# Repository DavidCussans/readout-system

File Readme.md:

SoLid readout system
====================

_Development of the readout system for the full scale SoLid experiment._

The repository is split into the separate development parts:

* sensors - The light sensors and the PCBs
* analog board - to provide bias voltage, amplify and shape the analog signals form the sensors
* digital board - to digitise the analog signals, analyse the signals in an FPGA to make trigger decisions and transmit them to a PC
* software - to collect data transmitted from the FPGA, further reduce the data and write it to disk. The interface for operators to control the system
* cabling - to connect the senors to the analog board, the analog board to the digital board, power supplies to each board, etc.
* docs - system level documents such as requirements, reports, etc.
* utility_box   design info and documentation about the utility box

Permissions
-----------

The `Readout developers` group have write access, other members of the collaboration have read access.
If you need access contact Dan Saunders.

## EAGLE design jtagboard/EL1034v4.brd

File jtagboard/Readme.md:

Documentation about JTAG board.

Design files in Eagle.

Cable needed to control multiplexer. See https://docs.google.com/spreadsheets/d/1sPC1HHSBhcLIxRam0Nl7j7j9OBzJNn8TZ3wjZsIO86E/edit?usp=sharing

Script to set up Minnowboard GPIO: setup_gpio.sh

Script to select which HDMI interface is used: test_jtag_mltxer.py

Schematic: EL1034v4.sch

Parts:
C1, C4, C36: 100u; EIA7343
C2, C3, C5, C6, C7, C8, C9, C10, C11, C12, C13, C14, C15, C16, C17, C18, C19, C20, C21, C22, C23, C24, C25, C26, C27, C28, C29, C30, C31, C32, C33, C34, C35, C37: 100n; 0805
CON1: SL5.08/2
D1, D2, D3, D4, D5, D6, D7, D8, D9: RED; LED-0603
HDMI0, HDMI1, HDMI2, HDMI3, HDMI4, HDMI5, HDMI6, HDMI7, HDMI8, HDMI9: 47266-0001
IC1, IC3, IC5, IC7, IC9, IC11, IC13, IC15, IC17, IC19: DS90LV031ATMX; SOIC127P600X175-16N
IC2, IC4, IC6, IC8, IC10, IC12, IC14, IC16, IC18, IC20: SN65LVDT2DBVT; SOT95P280X145-5N
IC21, IC22, IC23, IC24, IC25, IC26, IC27, IC28: 74LV4051PW; TSSOP16
IC29: LM3940; TO220-IGO
IC30: 74LVC1G14SE-7; SOT65P210X110-5N
JP1, JP2, JP3, JP4, JP5, JP6, JP7, JP8, JP9, JP10, JP11: M06POLAR; MOLEX-1X6
JP12, JP13: M02POLAR; MOLEX-1X2
MOD1: JTAG-SMT2; JTAG_SMT2
R1, R3, R5, R7, R9, R30, R32, R34, R36, R38, R40, R42, R44, R46, R48, R50, R52, R54, R56, R58, R60, R62, R64, R66, R68, R70, R72, R74, R76, R78: DNF; 0603-RES
R2, R4, R6, R8, R10, R31, R33, R35, R37, R39, R41, R43, R45, R47, R49, R51, R53, R55, R57, R59, R61, R63, R65, R67, R69, R71, R73, R75, R77, R79: 100k; 0603-RES
R11, R12, R13, R14, R15, R16, R17, R18, R19, R20: 10k; 0603-RES
R21, R22, R23, R24, R25, R26, R27, R28, R29: 2K2; 0603-RES
SJ1, SJ2, SJ3, SJ4, SJ5, SJ6, SJ7, SJ8, SJ9, SJ10, SJ11, SJ12, SJ13: SOLDERJUMPERNO; SJ_2S-NO
STANDOFF1, STANDOFF2, STANDOFF3, STANDOFF4, STANDOFF5, STANDOFF6, STANDOFF7: STAND-OFF
TP1, TP2: TEST-POINTTP_15TH_THRU; TP_15TH

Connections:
3.3V: C3.1, C4.A (+), C5.1, C6.1, C7.1, C8.1, C9.1, C10.1, C11.1, C12.1, C13.1, C14.2, C15.2, C16.2, C17.2, C18.2, C19.2, C20.2, C21.2, C22.2, C23.2, C24.2, C25.2, C26.2, C27.2, C28.2, C29.2, C30.2, C31.2, C32.2, C33.2, C34.2, C35.1, C36.A (+), C37.1, D9.A, IC1.4 (EN), IC1.16 (VCC), IC2.1 (VCC), IC3.4 (EN), IC3.16 (VCC), IC4.1 (VCC), IC5.4 (EN), IC5.16 (VCC), IC6.1 (VCC), IC7.4 (EN), IC7.16 (VCC), IC8.1 (VCC), IC9.4 (EN), IC9.16 (VCC), IC10.1 (VCC), IC11.4 (EN), IC11.16 (VCC), IC12.1 (VCC), IC13.4 (EN), IC13.16 (VCC), IC14.1 (VCC), IC15.4 (EN), IC15.16 (VCC), IC16.1 (VCC), IC17.4 (EN), IC17.16 (VCC), IC18.1 (VCC), IC19.4 (EN), IC19.16 (VCC), IC20.1 (VCC), IC21.16 (VCC), IC22.16 (VCC), IC23.16 (VCC), IC24.16 (VCC), IC25.16 (VCC), IC26.16 (VCC), IC27.16 (VCC), IC28.16 (VCC), IC29.OUT, IC30.5 (VCC), JP12.2, JP13.2, MOD1.9 (VREF), MOD1.11 (VDD), R1.2, R3.2, R5.2, R7.2, R9.2, R11.2, R12.2, R13.2, R14.2, R15.2, R16.2, R17.2, R18.2, R19.2, R20.2, R30.2, R32.2, R34.2, R36.2, R38.2, R40.2, R42.2, R44.2, R46.2, R48.2, R50.2, R52.2, R54.2, R56.2, R58.2, R60.2, R62.2, R64.2, R66.2, R68.2, R70.2, R72.2, R74.2, R76.2, R78.2, TP1.P$1
5V_IN: C1.A (+), C2.1, CON1.P$1, IC29.IN, JP1.2
!S3: IC22.6 (!E), IC24.6 (!E), IC26.6 (!E), IC28.6 (!E), IC30.4 (Y)
GND: C1.C (-), C2.2, C3.2, C4.C (-), C5.2, C6.2, C7.2, C8.2, C9.2, C10.2, C11.2, C12.2, C13.2, C14.1, C15.1, C16.1, C17.1, C18.1, C19.1, C20.1, C21.1, C22.1, C23.1, C24.1, C25.1, C26.1, C27.1, C28.1, C29.1, C30.1, C31.1, C32.1, C33.1, C34.1, C35.2, C36.C (-), C37.2, CON1.P$2, HDMI0.2, HDMI0.5, HDMI0.8, HDMI0.11, HDMI0.13, HDMI0.14, HDMI0.17, HDMI0.18, HDMI0.19, HDMI0.SHELL1, HDMI0.SHELL2, HDMI0.SHELL3, HDMI0.SHELL4, HDMI1.2, HDMI1.5, HDMI1.8, HDMI1.11, HDMI1.13, HDMI1.14, HDMI1.17, HDMI1.18, HDMI1.19, HDMI1.SHELL1, HDMI1.SHELL2, HDMI1.SHELL3, HDMI1.SHELL4, HDMI2.2, HDMI2.5, HDMI2.8, HDMI2.11, HDMI2.13, HDMI2.14, HDMI2.17, HDMI2.18, HDMI2.19, HDMI2.SHELL1, HDMI2.SHELL2, HDMI2.SHELL3, HDMI2.SHELL4, HDMI3.2, HDMI3.5, HDMI3.8, HDMI3.11, HDMI3.13, HDMI3.14, HDMI3.17, HDMI3.18, HDMI3.19, HDMI3.SHELL1, HDMI3.SHELL2, HDMI3.SHELL3, HDMI3.SHELL4, HDMI4.2, HDMI4.5, HDMI4.8, HDMI4.11, HDMI4.13, HDMI4.14, HDMI4.17, HDMI4.18, HDMI4.19, HDMI4.SHELL1, HDMI4.SHELL2, HDMI4.SHELL3, HDMI4.SHELL4, HDMI5.2, HDMI5.5, HDMI5.8, HDMI5.11, HDMI5.13, HDMI5.14, HDMI5.17, HDMI5.18, HDMI5.19, HDMI5.SHELL1, HDMI5.SHELL2, HDMI5.SHELL3, HDMI5.SHELL4, HDMI6.2, HDMI6.5, HDMI6.8, HDMI6.11, HDMI6.13, HDMI6.14, HDMI6.17, HDMI6.18, HDMI6.19, HDMI6.SHELL1, HDMI6.SHELL2, HDMI6.SHELL3, HDMI6.SHELL4, HDMI7.2, HDMI7.5, HDMI7.8, HDMI7.11, HDMI7.13, HDMI7.14, HDMI7.17, HDMI7.18, HDMI7.19, HDMI7.SHELL1, HDMI7.SHELL2, HDMI7.SHELL3, HDMI7.SHELL4, HDMI8.2, HDMI8.5, HDMI8.8, HDMI8.11, HDMI8.13, HDMI8.14, HDMI8.17, HDMI8.18, HDMI8.19, HDMI8.SHELL1, HDMI8.SHELL2, HDMI8.SHELL3, HDMI8.SHELL4, HDMI9.2, HDMI9.5, HDMI9.8, HDMI9.11, HDMI9.13, HDMI9.14, HDMI9.17, HDMI9.18, HDMI9.19, HDMI9.SHELL1, HDMI9.SHELL2, HDMI9.SHELL3, HDMI9.SHELL4, IC1.8 (GND), IC1.12 (~EN), IC2.2 (GND), IC3.8 (GND), IC3.12 (~EN), IC4.2 (GND), IC5.8 (GND), IC5.12 (~EN), IC6.2 (GND), IC7.8 (GND), IC7.12 (~EN), IC8.2 (GND), IC9.8 (GND), IC9.12 (~EN), IC10.2 (GND), IC11.8 (GND), IC11.12 (~EN), IC12.2 (GND), IC13.8 (GND), IC13.12 (~EN), IC14.2 (GND), IC15.8 (GND), IC15.12 (~EN), IC16.2 (GND), IC17.8 (GND), IC17.12 (~EN), IC18.2 (GND), IC19.8 (GND), IC19.12 (~EN), IC20.2 (GND), IC21.7 (VEE), IC21.8 (GND), IC22.7 (VEE), IC22.8 (GND), IC23.7 (VEE), IC23.8 (GND), IC24.7 (VEE), IC24.8 (GND), IC25.7 (VEE), IC25.8 (GND), IC26.7 (VEE), IC26.8 (GND), IC27.7 (VEE), IC27.8 (GND), IC28.7 (VEE), IC28.8 (GND), IC29.GND, IC30.3 (GND), JP1.1, JP2.1, JP3.1, JP4.1, JP5.1, JP6.1, JP7.1, JP8.1, JP9.1, JP10.1, JP11.1, JP12.1, JP13.1, MOD1.1 (GND), MOD1.10 (GND2), R2.1, R4.1, R6.1, R8.1, R10.1, R25.1, R31.1, R33.1, R35.1, R37.1, R39.1, R41.1, R43.1, R45.1, R47.1, R49.1, R51.1, R53.1, R55.1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
unnamed: D1.A, R21.1
unnamed: D2.A, R22.1
unnamed: D3.A, R23.1
unnamed: D4.A, R24.1
unnamed: D9.C, SJ13.1
unnamed: D5.A, R26.1
unnamed: D6.A, R27.1
unnamed: D7.A, R28.1
unnamed: D8.A, R29.1
unnamed: R25.2, SJ13.2
unnamed: D1.C, D2.C, D3.C, D4.C, SJ11.1
unnamed: D5.C, D6.C, D7.C, D8.C, SJ12.1
unnamed: HDMI1.10, IC3.10 (DOUT3+)
unnamed: HDMI1.12, IC3.11 (DOUT3-)
unnamed: HDMI1.7, IC3.6 (DOUT2+)
unnamed: HDMI1.9, IC3.5 (DOUT2-)
unnamed: HDMI1.15, IC3.14 (DOUT4+)
unnamed: HDMI1.16, IC3.13 (DOUT4-)
unnamed: HDMI1.6, IC3.3 (DOUT1-)
unnamed: HDMI1.4, IC3.2 (DOUT1+)
unnamed: HDMI2.10, IC5.10 (DOUT3+)
unnamed: HDMI2.12, IC5.11 (DOUT3-)
unnamed: HDMI2.7, IC5.6 (DOUT2+)
unnamed: HDMI2.9, IC5.5 (DOUT2-)
unnamed: HDMI2.15, IC5.14 (DOUT4+)
unnamed: HDMI2.16, IC5.13 (DOUT4-)
unnamed: HDMI2.6, IC5.3 (DOUT1-)
unnamed: HDMI2.4, IC5.2 (DOUT1+)
unnamed: HDMI3.10, IC7.10 (DOUT3+)
unnamed: HDMI3.12, IC7.11 (DOUT3-)
unnamed: HDMI3.7, IC7.6 (DOUT2+)
unnamed: HDMI3.9, IC7.5 (DOUT2-)
unnamed: HDMI3.15, IC7.14 (DOUT4+)
unnamed: HDMI3.16, IC7.13 (DOUT4-)
unnamed: HDMI3.6, IC7.3 (DOUT1-)
unnamed: HDMI3.4, IC7.2 (DOUT1+)
unnamed: HDMI4.10, IC9.10 (DOUT3+)
unnamed: HDMI4.12, IC9.11 (DOUT3-)
unnamed: HDMI4.7, IC9.6 (DOUT2+)
unnamed: HDMI4.9, IC9.5 (DOUT2-)
unnamed: HDMI4.15, IC9.14 (DOUT4+)
unnamed: HDMI4.16, IC9.13 (DOUT4-)
unnamed: HDMI4.6, IC9.3 (DOUT1-)
unnamed: HDMI4.4, IC9.2 (DOUT1+)
unnamed: HDMI5.10, IC11.10 (DOUT3+)
unnamed: HDMI5.12, IC11.11 (DOUT3-)
unnamed: HDMI5.7, IC11.6 (DOUT2+)
unnamed: HDMI5.9, IC11.5 (DOUT2-)
unnamed: HDMI5.15, IC11.14 (DOUT4+)
unnamed: HDMI5.16, IC11.13 (DOUT4-)
unnamed: HDMI5.6, IC11.3 (DOUT1-)
unnamed: HDMI5.4, IC11.2 (DOUT1+)
unnamed: HDMI6.10, IC13.10 (DOUT3+)
unnamed: HDMI6.12, IC13.11 (DOUT3-)
unnamed: HDMI6.7, IC13.6 (DOUT2+)
unnamed: HDMI6.9, IC13.5 (DOUT2-)
unnamed: HDMI6.15, IC13.14 (DOUT4+)
unnamed: HDMI6.16, IC13.13 (DOUT4-)
unnamed: HDMI6.6, IC13.3 (DOUT1-)
unnamed: HDMI6.4, IC13.2 (DOUT1+)
unnamed: HDMI7.10, IC15.10 (DOUT3+)
unnamed: HDMI7.12, IC15.11 (DOUT3-)
unnamed: HDMI7.7, IC15.6 (DOUT2+)
unnamed: HDMI7.9, IC15.5 (DOUT2-)
unnamed: HDMI7.15, IC15.14 (DOUT4+)
unnamed: HDMI7.16, IC15.13 (DOUT4-)
unnamed: HDMI7.6, IC15.3 (DOUT1-)
unnamed: HDMI7.4, IC15.2 (DOUT1+)
unnamed: HDMI8.10, IC17.10 (DOUT3+)
unnamed: HDMI8.12, IC17.11 (DOUT3-)
unnamed: HDMI8.7, IC17.6 (DOUT2+)
unnamed: HDMI8.9, IC17.5 (DOUT2-)
unnamed: HDMI8.15, IC17.14 (DOUT4+)
unnamed: HDMI8.16, IC17.13 (DOUT4-)
unnamed: HDMI8.6, IC17.3 (DOUT1-)
unnamed: HDMI8.4, IC17.2 (DOUT1+)
unnamed: HDMI9.10, IC19.10 (DOUT3+)
unnamed: HDMI9.12, IC19.11 (DOUT3-)
unnamed: HDMI9.7, IC19.6 (DOUT2+)
unnamed: HDMI9.9, IC19.5 (DOUT2-)
unnamed: HDMI9.15, IC19.14 (DOUT4+)
unnamed: HDMI9.16, IC19.13 (DOUT4-)
unnamed: HDMI9.6, IC19.3 (DOUT1-)
unnamed: HDMI9.4, IC19.2 (DOUT1+)
PGOOD_0: IC1.15 (DIN4), JP2.6, R11.1, SJ1.1
PGOOD_0_P: HDMI0.15, IC1.14 (DOUT4+)
PGOOD_1: IC3.15 (DIN4), JP2.5, R12.1, SJ2.1
PGOOD_2: IC5.15 (DIN4), JP2.4, R13.1, SJ3.2
PGOOD_3: IC7.15 (DIN4), JP2.3, R14.1, SJ4.2
PGOOD_4: IC9.15 (DIN4), JP2.2, R15.1, SJ5.2
PGOOD_5: IC11.15 (DIN4), JP11.6, R16.1, SJ6.1
PGOOD_6: IC13.15 (DIN4), JP11.5, R17.1, SJ7.1
PGOOD_7: IC15.15 (DIN4), JP11.4, R18.1, SJ8.1
PGOOD_8: IC17.15 (DIN4), JP11.3, R19.1, SJ9.1
PGOOD_9: IC19.15 (DIN4), JP11.2, R20.1, SJ10.1
PGOOG_0_N: HDMI0.16, IC1.13 (DOUT4-)
S0: IC21.11 (S0), IC22.11 (S0), IC23.11 (S0), IC24.11 (S0), IC25.11 (S0), IC26.11 (S0), IC27.11 (S0), IC28.11 (S0), JP1.6, R21.2
S1: IC21.10 (S1), IC22.10 (S1), IC23.10 (S1), IC24.10 (S1), IC25.10 (S1), IC26.10 (S1), IC27.10 (S1), IC28.10 (S1), JP1.5, R22.2
S2: IC21.9 (S2), IC22.9 (S2), IC23.9 (S2), IC24.9 (S2), IC25.9 (S2), IC26.9 (S2), IC27.9 (S2), IC28.9 (S2), JP1.4, R23.2
S3: IC21.6 (!E), IC23.6 (!E), IC25.6 (!E), IC27.6 (!E), IC30.2 (A), JP1.3, R24.2
TCK: IC21.3 (Z), IC22.3 (Z), MOD1.2 (TCK), R26.2
TCK_0: IC1.1 (DIN1), IC21.13 (Y0), R1.1, R2.2
TCK_0_NEG: HDMI0.6, IC1.3 (DOUT1-)
TCK_0_POS: HDMI0.4, IC1.2 (DOUT1+)
TCK_1: IC3.1 (DIN1), IC21.14 (Y1), R7.1, R8.2
TCK_2: IC5.1 (DIN1), IC21.15 (Y2), R32.1, R33.2
TCK_3: IC7.1 (DIN1), IC21.12 (Y3), R38.1, R39.2
TCK_4: IC9.1 (DIN1), IC21.1 (Y4), R44.1, R45.2
TCK_5: IC21.5 (Y5), JP3.6
TCK_5_2: IC11.1 (DIN1), JP4.6, R50.1, R51.2
TCK_6: IC21.2 (Y6), JP3.5
TCK_6_2: IC13.1 (DIN1), JP4.5, R56.1, R57.2
TCK_7: IC21.4 (Y7), JP3.4
TCK_7_2: IC15.1 (DIN1), JP4.4, R62.1, R63.2
TCK_8: IC22.13 (Y0), JP3.3
TCK_8_2: IC17.1 (DIN1), JP4.3, R68.1, R69.2
TCK_9: IC22.14 (Y1), JP3.2
TCK_9_2: IC19.1 (DIN1), JP4.2, R74.1, R75.2
TDI: IC23.3 (Z), IC24.3 (Z), MOD1.3 (TDI), R27.2
TDI_0: IC1.9 (DIN3), IC23.13 (Y0), R5.1, R6.2
TDI_0_N: HDMI0.12, IC1.11 (DOUT3-)
TDI_0_P: HDMI0.10, IC1.10 (DOUT3+)
TDI_1: IC3.9 (DIN3), IC23.14 (Y1), R30.1, R31.2
TDI_2: IC5.9 (DIN3), IC23.15 (Y2), R36.1, R37.2
TDI_3: IC7.9 (DIN3), IC23.12 (Y3), R42.1, R43.2
TDI_4: IC9.9 (DIN3), IC23.1 (Y4), R48.1, R49.2
TDI_5: IC23.5 (Y5), JP5.6
TDI_5_2: IC11.9 (DIN3), JP6.6, R54.1, R55.2
TDI_6: IC23.2 (Y6), JP5.5
TDI_6_2: IC13.9 (DIN3), JP6.5, R60.1, R61.2
TDI_7: IC23.4 (Y7), JP5.4
TDI_7_2: IC15.9 (DIN3), JP6.4, R66.1, R67.2
TDI_8: IC24.13 (Y0), JP5.3
TDI_8_2: IC17.9 (DIN3), JP6.3, R72.1, R73.2
TDI_9: IC24.14 (Y1), JP5.2
TDI_9_2: IC19.9 (DIN3), JP6.2, R78.1, R79.2
TDO: IC27.3 (Z), IC28.3 (Z), MOD1.8 (TDO), R29.2
TDO_0: IC2.5 (R), IC27.13 (Y0)
TDO_0_N: HDMI0.3, IC2.4 (B)
TDO_0_P: HDMI0.1, IC2.3 (A)
TDO_1: IC4.5 (R), IC27.14 (Y1)
TDO_1_N: HDMI1.3, IC4.4 (B)
TDO_1_P: HDMI1.1, IC4.3 (A)
TDO_2: IC6.5 (R), IC27.15 (Y2)
TDO_2_N: HDMI2.3, IC6.4 (B)
TDO_2_P: HDMI2.1, IC6.3 (A)
TDO_3: IC8.5 (R), IC27.12 (Y3)
TDO_3_N: HDMI3.3, IC8.4 (B)
TDO_3_P: HDMI3.1, IC8.3 (A)
TDO_4: IC10.5 (R), IC27.1 (Y4)
TDO_4_N: HDMI4.3, IC10.4 (B)
TDO_4_P: HDMI4.1, IC10.3 (A)
TDO_5: IC27.5 (Y5), JP9.6
TDO_5_2: IC12.5 (R), JP10.6
TDO_5_N: HDMI5.3, IC12.4 (B)
TDO_5_P: HDMI5.1, IC12.3 (A)
TDO_6: IC27.2 (Y6), JP9.5
TDO_6_2: IC14.5 (R), JP10.5
TDO_6_N: HDMI6.3, IC14.4 (B)
TDO_6_P: HDMI6.1, IC14.3 (A)
TDO_7: IC27.4 (Y7), JP9.4
TDO_7_2: IC16.5 (R), JP10.4
TDO_7_N: HDMI7.3, IC16.4 (B)
TDO_7_P: HDMI7.1, IC16.3 (A)
TDO_8: IC28.13 (Y0), JP9.3
TDO_8_2: IC18.5 (R), JP10.3
TDO_8_N: HDMI8.3, IC18.4 (B)
TDO_8_P: HDMI8.1, IC18.3 (A)
TDO_9: IC28.14 (Y1), JP9.2
TDO_9_2: IC20.5 (R), JP10.2
TDO_9_N: HDMI9.3, IC20.4 (B)
TDO_9_P: HDMI9.1, IC20.3 (A)
TMS: IC25.3 (Z), IC26.3 (Z), MOD1.4 (TMS), R28.2
TMS_0: IC1.7 (DIN2), IC25.13 (Y0), R3.1, R4.2
TMS_0_N: HDMI0.9, IC1.5 (DOUT2-)
TMS_0_P: HDMI0.7, IC1.6 (DOUT2+)
TMS_1: IC3.7 (DIN2), IC25.14 (Y1), R9.1, R10.2
TMS_2: IC5.7 (DIN2), IC25.15 (Y2), R34.1, R35.2
TMS_3: IC7.7 (DIN2), IC25.12 (Y3), R40.1, R41.2
TMS_4: IC9.7 (DIN2), IC25.1 (Y4), R46.1, R47.2
TMS_5: IC25.5 (Y5), JP7.6
TMS_5_2: IC11.7 (DIN2), JP8.6, R52.1, R53.2
TMS_6: IC25.2 (Y6), JP7.5
TMS_6_2: IC13.7 (DIN2), JP8.5, R58.1, R59.2
TMS_7: IC25.4 (Y7), JP7.4
TMS_7_2: IC15.7 (DIN2), JP8.4, R64.1, R65.2
TMS_8: IC26.13 (Y0), JP7.3
TMS_8_2: IC17.7 (DIN2), JP8.3, R70.1, R71.2
TMS_9: IC26.14 (Y1), JP7.2
TMS_9_2: IC19.7 (DIN2), JP8.2, R76.1, R77.2

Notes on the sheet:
ADDRESS INPUT FROM CONTROLLER
Change Log from V1
Replaced DS90C031 (5V) with DS90LV031ATMX (3v3)
Removed redundant 100R terminators on SN65LVDT2 ICs
Added SJ 11, 12 & 13 to deactivate diagnostic LEDs
Added weak pull-downs on multiplexer outputs and positions for weak pull-ups instead.
Added 5v supply to address input to provide external power
Changed electrolytic caps to tantalum for more stable ESR with temperature to ensure 3.3v regulator stability
Removed spare mounting hole
Rerouted GND traces between pins of HDMI connectors
Change Log from V3
V3 used 'Cream' layer to generate solder mask which left NO solder jumpers covered. V4 uses 'Stop' layer instead.

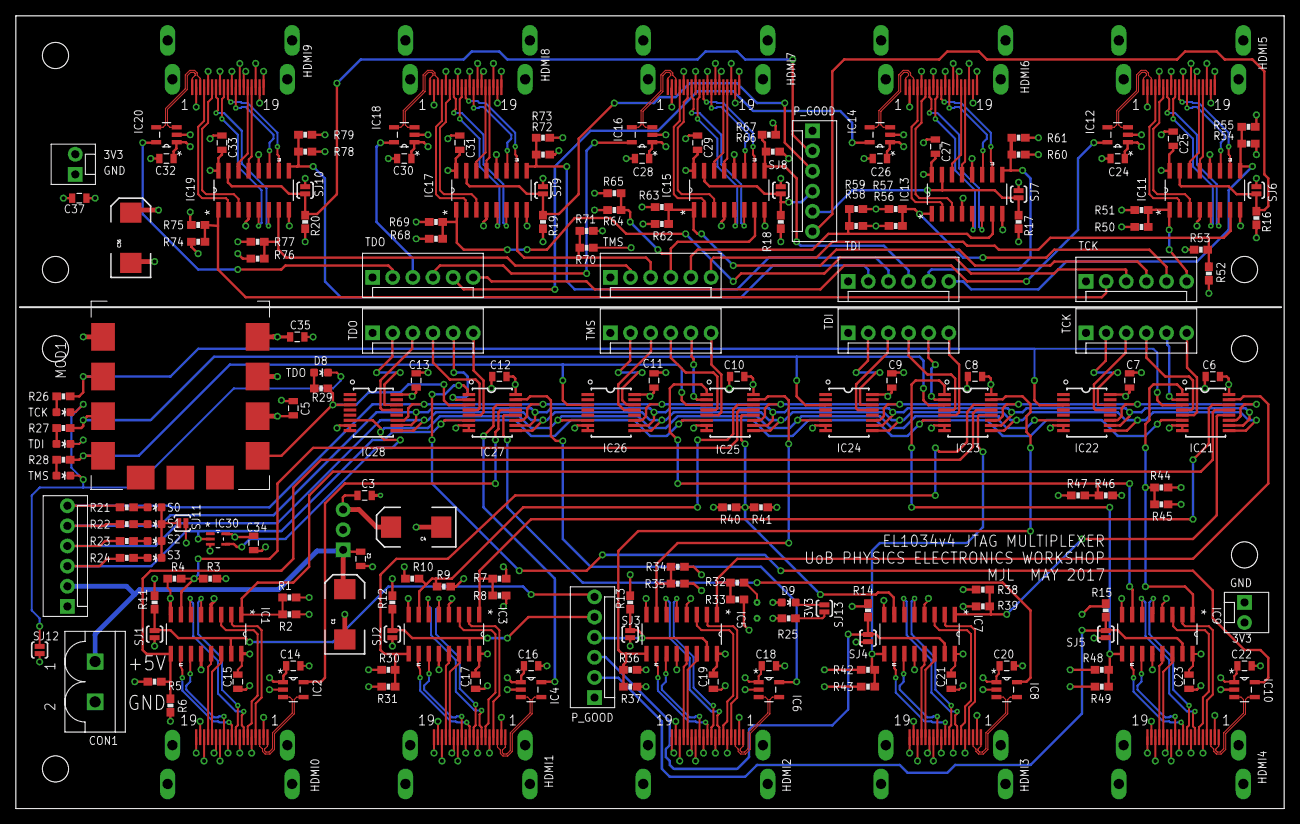
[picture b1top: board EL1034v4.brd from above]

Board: 4 copper layers, 160.0 x 100.0 mm, 202 parts (1 on the bottom side), 194 nets.

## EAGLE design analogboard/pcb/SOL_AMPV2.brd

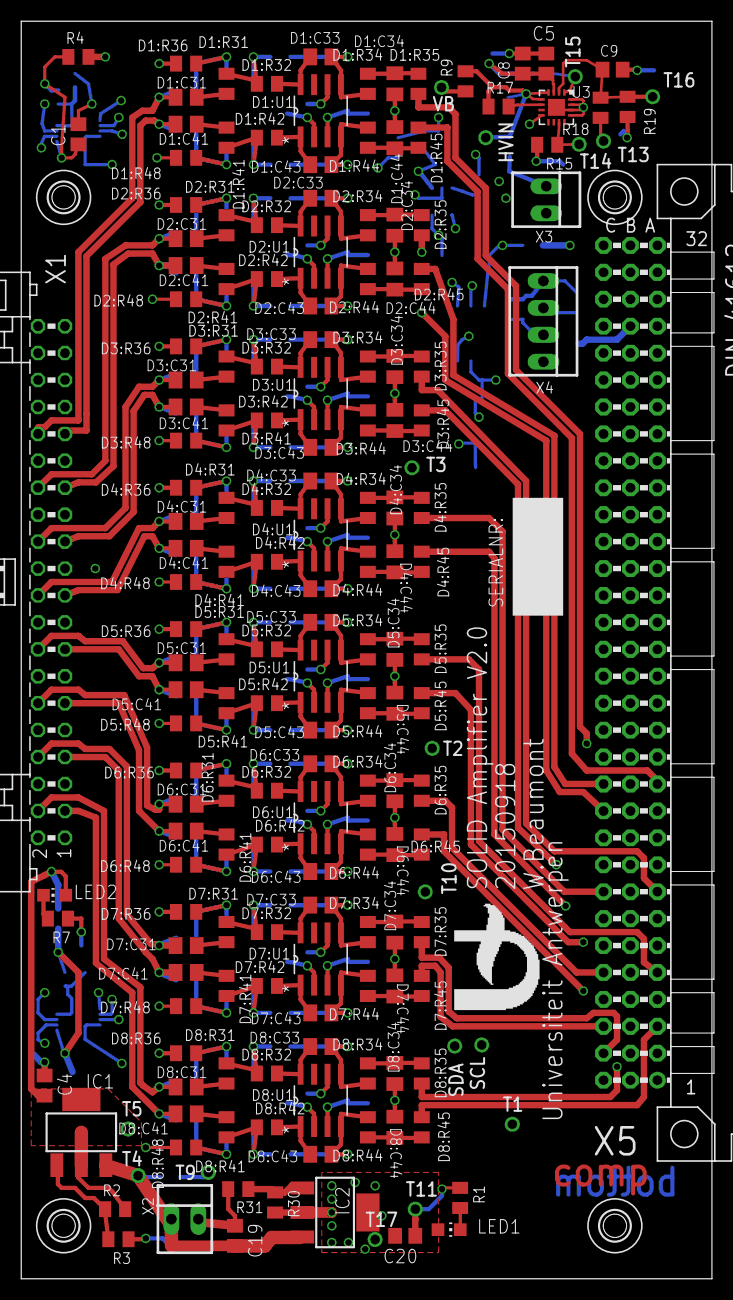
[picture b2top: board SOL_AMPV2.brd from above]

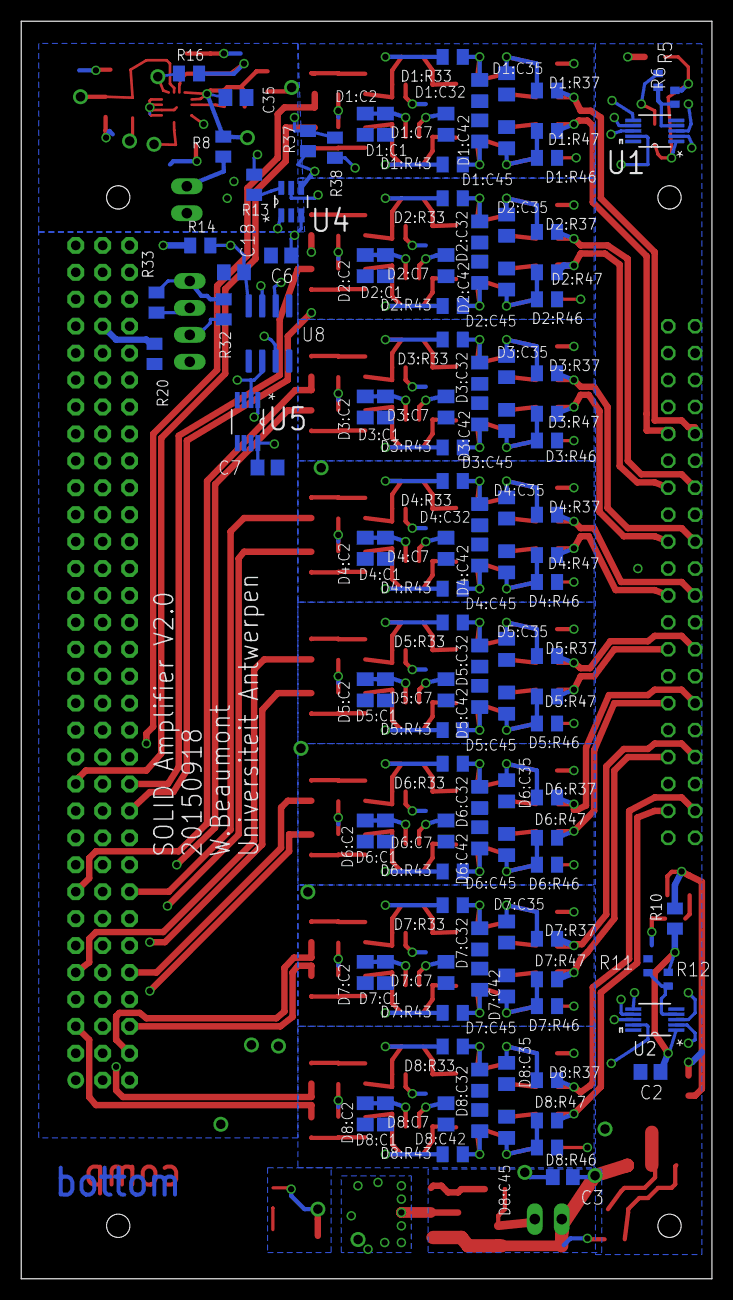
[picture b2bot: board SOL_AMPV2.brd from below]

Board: 4 copper layers, 65.2 x 118.6 mm, 308 parts (121 on the bottom side), 172 nets.

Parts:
C1, C2: 10u; C0805
C3, C4, C19, C20: 10uF; C0805
C5, C6, C7, C9, C18: 10n; C0805
C8: 100n; C0805
C35: 100nF /100V; C0805K
D1:C1, D2:C1, D3:C1, D4:C1, D5:C1, D6:C1, D7:C1, D8:C1: 100n; C0805K
D1:C2, D1:C7, D2:C2, D2:C7, D3:C2, D3:C7, D4:C2, D4:C7, D5:C2, D5:C7, D6:C2, D6:C7, D7:C2, D7:C7, D8:C2, D8:C7: 10n; C0805K
D1:C31, D2:C31, D3:C31, D4:C31, D5:C31, D6:C31, D7:C31, D8:C31: 4.4n/100V; C0805K
D1:C32, D1:C42, D2:C32, D2:C42, D3:C32, D3:C42, D4:C32, D4:C42, D5:C32, D5:C42, D6:C32, D6:C42, D7:C32, D7:C42, D8:C32, D8:C42: 152p; C0805K
D1:C33, D1:C43, D2:C33, D2:C43, D3:C33, D3:C43, D4:C33, D4:C43, D5:C33, D5:C43, D6:C33, D6:C43, D7:C33, D7:C43, D8:C33, D8:C43: 21p; C0805K
D1:C34, D1:C44, D2:C34, D2:C44, D3:C34, D3:C44, D4:C34, D4:C44, D5:C34, D5:C44, D6:C34, D6:C44, D7:C34, D7:C44, D8:C34, D8:C44: x; C0805K
D1:C35, D1:C45, D2:C35, D2:C45, D3:C35, D3:C45, D4:C35, D4:C45, D5:C35, D5:C45, D6:C35, D6:C45, D7:C35, D7:C45, D8:C35, D8:C45: 100nF /100V; C0805K
D1:C41, D2:C41, D3:C41, D4:C41, D5:C41, D6:C41, D7:C41, D8:C41: 4.4n; C0805K
D1:R31, D1:R41, D2:R31, D2:R41, D3:R31, D3:R41, D4:R31, D4:R41, D5:R31, D5:R41, D6:R31, D6:R41, D7:R31, D7:R41, D8:R31, D8:R41: 27; R0805H
D1:R32, D1:R42, D2:R32, D2:R42, D3:R32, D3:R42, D4:R32, D4:R42, D5:R32, D5:R42, D6:R32, D6:R42, D7:R32, D7:R42, D8:R32, D8:R42: 24; R0805H
D1:R33, D1:R43, D2:R33, D2:R43, D3:R33, D3:R43, D4:R33, D4:R43, D5:R33, D5:R43, D6:R33, D6:R43, D7:R33, D7:R43, D8:R33, D8:R43: 3K; R0805H
D1:R34, D1:R35, D1:R44, D1:R45, D2:R34, D2:R35, D2:R44, D2:R45, D3:R34, D3:R35, D3:R44, D3:R45, D4:R34, D4:R35, D4:R44, D4:R45, D5:R34, D5:R35, D5:R44, D5:R45, D6:R34, D6:R35, D6:R44, D6:R45, D7:R34, D7:R35, D7:R44, D7:R45, D8:R34, D8:R35, D8:R44, D8:R45: 1; R0805H
D1:R36, D1:R46, D2:R36, D2:R46, D3:R36, D3:R46, D4:R36, D4:R46, D5:R36, D5:R46, D6:R36, D6:R46, D7:R36, D7:R46, D8:R36, D8:R46: 10K; R0805H
D1:R37, D1:R47, D2:R37, D2:R47, D3:R37, D3:R47, D4:R37, D4:R47, D5:R37, D5:R47, D6:R37, D6:R47, D7:R37, D7:R47, D8:R37, D8:R47: 100K; R0805H
D1:R48, D2:R48, D3:R48, D4:R48, D5:R48, D6:R48, D7:R48, D8:R48: 470; R0805H
D1:U1, D2:U1, D3:U1, D4:U1, D5:U1, D6:U1, D7:U1, D8:U1: AD8132ARZ; SOIC127P600X175-8N
H1, H2, H3, H4: 2,1
HVIN: UA_TPPAD1-13; UA_P1-13
IC1, IC2: LM1117; SOT223
LED1, LED2: HSMY-C170; CHIP-LED0805
M1: UA
R1, R3, R7, R8, R16, R18, R31: 1K; R0805H
R2, R30: 330E; R0805H
R4: 10E; R0805H
R5, R11: 0E; R0402
R6, R12: NC; R0402
R9, R14, R17: NC; R0805H
R10: 10; R0805H
R13, R32, R33, R37, R38: 4K7; R0805H
R15: 27K; R0805H
R19: 2.4K; R0805H
R20: 0; R0805H
SCL: UA_TPPAD1-13; UA_P1-13
SDA: UA_TPPAD1-13; UA_P1-13
T1, T2, T3, T4, T5, T9, T10, T11, T13, T14, T15, T16, T17: UA_TPPAD1-13; UA_P1-13
U1, U2: MCP4728-E/UN; SOP50P490X110-10N
U3: ADL5317; LFCSP_LQ-16_MANSOL
U4: MCP4725A0T-E/CH; SOT95P270X145-6N
U5: MCP9808-E/MS; SOP65P490X110-8N
U8: P82B715TD; SO8
VB: UA_TPPAD1-13; UA_P1-13
X1: 40pin; ML40L
X2, X3: 22-23-2021
X4: 22-23-2041
X5: DIN41612_ABC_96_R; DIN41612_96RC

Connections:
BIASSET: C9.1, R18.2, R19.1, T16.TP, U3.2
BIASTRSET: R18.1, T13.TP, U4.1
D1:AOUT+: D1:C43.2, D1:R43.2, D1:R44.1, D1:U1.4
D1:AOUT-: D1:C33.2, D1:R33.2, D1:R34.1, D1:U1.5
D1:FB+: D1:C32.2, D1:R31.2, D1:R32.1, D1:R33.1
D1:FB-: D1:C42.2, D1:R41.2, D1:R42.1, D1:R43.1
D1:N$1: D1:C34.2, D1:R34.2, D1:R35.1
D1:N$2: D1:C7.1, D1:U1.2
D1:N$3: D1:C44.2, D1:R44.2, D1:R45.1
D1:N$4: D1:C43.1, D1:R42.2, D1:U1.1
D1:N$5: D1:C33.1, D1:R32.2, D1:U1.8
D1:N$10: D1:C41.1, D1:R41.1
D1:R31: D1:C31.1, D1:R31.1
D1:VB+: D1:C35.1, D1:R36.1, D1:R37.2
D1:VB-: D1:C45.1, D1:R46.2, D1:R47.1, D1:R48.2
D2:AOUT+: D2:C43.2, D2:R43.2, D2:R44.1, D2:U1.4
D2:AOUT-: D2:C33.2, D2:R33.2, D2:R34.1, D2:U1.5
D2:FB+: D2:C32.2, D2:R31.2, D2:R32.1, D2:R33.1
D2:FB-: D2:C42.2, D2:R41.2, D2:R42.1, D2:R43.1
D2:N$1: D2:C34.2, D2:R34.2, D2:R35.1
D2:N$2: D2:C7.1, D2:U1.2
D2:N$3: D2:C44.2, D2:R44.2, D2:R45.1
D2:N$4: D2:C43.1, D2:R42.2, D2:U1.1
D2:N$5: D2:C33.1, D2:R32.2, D2:U1.8
D2:N$10: D2:C41.1, D2:R41.1
D2:R31: D2:C31.1, D2:R31.1
D2:VB+: D2:C35.1, D2:R36.1, D2:R37.2
D2:VB-: D2:C45.1, D2:R46.2, D2:R47.1, D2:R48.2
D3:AOUT+: D3:C43.2, D3:R43.2, D3:R44.1, D3:U1.4
D3:AOUT-: D3:C33.2, D3:R33.2, D3:R34.1, D3:U1.5
D3:FB+: D3:C32.2, D3:R31.2, D3:R32.1, D3:R33.1
D3:FB-: D3:C42.2, D3:R41.2, D3:R42.1, D3:R43.1
D3:N$1: D3:C34.2, D3:R34.2, D3:R35.1
D3:N$2: D3:C7.1, D3:U1.2
D3:N$3: D3:C44.2, D3:R44.2, D3:R45.1
D3:N$4: D3:C43.1, D3:R42.2, D3:U1.1
D3:N$5: D3:C33.1, D3:R32.2, D3:U1.8
D3:N$10: D3:C41.1, D3:R41.1
D3:R31: D3:C31.1, D3:R31.1
D3:VB+: D3:C35.1, D3:R36.1, D3:R37.2
D3:VB-: D3:C45.1, D3:R46.2, D3:R47.1, D3:R48.2
D4:AOUT+: D4:C43.2, D4:R43.2, D4:R44.1, D4:U1.4
D4:AOUT-: D4:C33.2, D4:R33.2, D4:R34.1, D4:U1.5
D4:FB+: D4:C32.2, D4:R31.2, D4:R32.1, D4:R33.1
D4:FB-: D4:C42.2, D4:R41.2, D4:R42.1, D4:R43.1
D4:N$1: D4:C34.2, D4:R34.2, D4:R35.1
D4:N$2: D4:C7.1, D4:U1.2
D4:N$3: D4:C44.2, D4:R44.2, D4:R45.1
D4:N$4: D4:C43.1, D4:R42.2, D4:U1.1
D4:N$5: D4:C33.1, D4:R32.2, D4:U1.8
D4:N$10: D4:C41.1, D4:R41.1
D4:R31: D4:C31.1, D4:R31.1
D4:VB+: D4:C35.1, D4:R36.1, D4:R37.2
D4:VB-: D4:C45.1, D4:R46.2, D4:R47.1, D4:R48.2
D5:AOUT+: D5:C43.2, D5:R43.2, D5:R44.1, D5:U1.4
D5:AOUT-: D5:C33.2, D5:R33.2, D5:R34.1, D5:U1.5
D5:FB+: D5:C32.2, D5:R31.2, D5:R32.1, D5:R33.1
D5:FB-: D5:C42.2, D5:R41.2, D5:R42.1, D5:R43.1
D5:N$1: D5:C34.2, D5:R34.2, D5:R35.1
D5:N$2: D5:C7.1, D5:U1.2
D5:N$3: D5:C44.2, D5:R44.2, D5:R45.1
D5:N$4: D5:C43.1, D5:R42.2, D5:U1.1
D5:N$5: D5:C33.1, D5:R32.2, D5:U1.8
D5:N$10: D5:C41.1, D5:R41.1
D5:R31: D5:C31.1, D5:R31.1
D5:VB+: D5:C35.1, D5:R36.1, D5:R37.2
D5:VB-: D5:C45.1, D5:R46.2, D5:R47.1, D5:R48.2
D6:AOUT+: D6:C43.2, D6:R43.2, D6:R44.1, D6:U1.4
D6:AOUT-: D6:C33.2, D6:R33.2, D6:R34.1, D6:U1.5
D6:FB+: D6:C32.2, D6:R31.2, D6:R32.1, D6:R33.1
D6:FB-: D6:C42.2, D6:R41.2, D6:R42.1, D6:R43.1
D6:N$1: D6:C34.2, D6:R34.2, D6:R35.1
D6:N$2: D6:C7.1, D6:U1.2
D6:N$3: D6:C44.2, D6:R44.2, D6:R45.1
D6:N$4: D6:C43.1, D6:R42.2, D6:U1.1
D6:N$5: D6:C33.1, D6:R32.2, D6:U1.8
D6:N$10: D6:C41.1, D6:R41.1
D6:R31: D6:C31.1, D6:R31.1
D6:VB+: D6:C35.1, D6:R36.1, D6:R37.2
D6:VB-: D6:C45.1, D6:R46.2, D6:R47.1, D6:R48.2
D7:AOUT+: D7:C43.2, D7:R43.2, D7:R44.1, D7:U1.4
D7:AOUT-: D7:C33.2, D7:R33.2, D7:R34.1, D7:U1.5
D7:FB+: D7:C32.2, D7:R31.2, D7:R32.1, D7:R33.1
D7:FB-: D7:C42.2, D7:R41.2, D7:R42.1, D7:R43.1
D7:N$1: D7:C34.2, D7:R34.2, D7:R35.1
D7:N$2: D7:C7.1, D7:U1.2
D7:N$3: D7:C44.2, D7:R44.2, D7:R45.1
D7:N$4: D7:C43.1, D7:R42.2, D7:U1.1
D7:N$5: D7:C33.1, D7:R32.2, D7:U1.8
D7:N$10: D7:C41.1, D7:R41.1
D7:R31: D7:C31.1, D7:R31.1
D7:VB+: D7:C35.1, D7:R36.1, D7:R37.2
D7:VB-: D7:C45.1, D7:R46.2, D7:R47.1, D7:R48.2
D8:AOUT+: D8:C43.2, D8:R43.2, D8:R44.1, D8:U1.4
D8:AOUT-: D8:C33.2, D8:R33.2, D8:R34.1, D8:U1.5
D8:FB+: D8:C32.2, D8:R31.2, D8:R32.1, D8:R33.1
D8:FB-: D8:C42.2, D8:R41.2, D8:R42.1, D8:R43.1
D8:N$1: D8:C34.2, D8:R34.2, D8:R35.1
D8:N$2: D8:C7.1, D8:U1.2
D8:N$3: D8:C44.2, D8:R44.2, D8:R45.1
D8:N$4: D8:C43.1, D8:R42.2, D8:U1.1
D8:N$5: D8:C33.1, D8:R32.2, D8:U1.8
D8:N$10: D8:C41.1, D8:R41.1
D8:R31: D8:C31.1, D8:R31.1
D8:VB+: D8:C35.1, D8:R36.1, D8:R37.2
D8:VB-: D8:C45.1, D8:R46.2, D8:R47.1, D8:R48.2
GND: C1.2, C2.2, C3.1, C4.1, C5.2, C6.2, C7.2, C8.2, C9.2, C18.2, C19.1, C20.1, C35.2, D1:C1.1, D1:C2.1, D1:C7.2, D1:C32.1, D1:C34.1, D1:C35.2, D1:C42.1, D1:C44.1, D1:C45.2, D1:R46.1, D1:U1.6, D2:C1.1, D2:C2.1, D2:C7.2, D2:C32.1, D2:C34.1, D2:C35.2, D2:C42.1, D2:C44.1, D2:C45.2, D2:R46.1, D2:U1.6, D3:C1.1, D3:C2.1, D3:C7.2, D3:C32.1, D3:C34.1, D3:C35.2, D3:C42.1, D3:C44.1, D3:C45.2, D3:R46.1, D3:U1.6, D4:C1.1, D4:C2.1, D4:C7.2, D4:C32.1, D4:C34.1, D4:C35.2, D4:C42.1, D4:C44.1, D4:C45.2, D4:R46.1, D4:U1.6, D5:C1.1, D5:C2.1, D5:C7.2, D5:C32.1, D5:C34.1, D5:C35.2, D5:C42.1, D5:C44.1, D5:C45.2, D5:R46.1, D5:U1.6, D6:C1.1, D6:C2.1, D6:C7.2, D6:C32.1, D6:C34.1, D6:C35.2, D6:C42.1, D6:C44.1, D6:C45.2, D6:R46.1, D6:U1.6, D7:C1.1, D7:C2.1, D7:C7.2, D7:C32.1, D7:C34.1, D7:C35.2, D7:C42.1, D7:C44.1, D7:C45.2, D7:R46.1, D7:U1.6, D8:C1.1, D8:C2.1, D8:C7.2, D8:C32.1, D8:C34.1, D8:C35.2, D8:C42.1, D8:C44.1, D8:C45.2, D8:R46.1, D8:U1.6, R1.1, R3.1, R5.1, R7.1, R11.1, R15.2, R19.2, R20.1, R31.1, T1.TP, T2.TP, T3.TP, T9.TP, T10.TP, T11.TP, U1.10, U2.10, U3.13, U3.14, U3.15, U3.16, U3.EXP, U4.2, U5.4, U5.5, U5.6, U5.7, U8.4, X1.1, X1.2, X1.5, X1.6, X1.9, X1.10, X1.13, X1.14, X1.17, X1.18, X1.21, X1.22, X1.25, X1.26, X1.29, X1.30, X1.33, X1.34, X1.39, X1.40, X2.2, X3.2, X4.4, X5.A1, X5.A4, X5.A7, X5.A10, X5.A13, X5.A16, X5.A19, X5.A22, X5.A25, X5.A28, X5.B1, X5.B2, X5.B3, X5.B4, X5.B5, X5.B6, X5.B7, X5.B8, X5.B9, X5.B10, X5.B11, X5.B12, X5.B13, X5.B14, X5.B15, X5.B16, X5.B17, X5.B18, X5.B19, X5.B20, X5.B21, X5.B22, X5.B23, X5.B24, X5.B25, X5.B26, X5.B27, X5.B28, X5.C1, X5.C4, X5.C7, X5.C10, X5.C13, X5.C16, X5.C19, X5.C22, X5.C25, X5.C28
HVIN: C35.1, HVIN.TP, R8.1, R9.2, R17.1, U3.4, U3.5
IN0: D1:C41.2, D1:R47.2, X1.31
IN1: D2:C41.2, D2:R47.2, X1.27
IN2: D3:C41.2, D3:R47.2, X1.23
IN3: D4:C41.2, D4:R47.2, X1.19
IN4: D5:C41.2, D5:R47.2, X1.15
IN5: D6:C41.2, D6:R47.2, X1.11
IN6: D7:C41.2, D7:R47.2, X1.7
IN7: D8:C41.2, D8:R47.2, X1.3
IP0: D1:C31.2, D1:R37.1, X1.32
IP1: D2:C31.2, D2:R37.1, X1.28
IP2: D3:C31.2, D3:R37.1, X1.24
IP3: D4:C31.2, D4:R37.1, X1.20
IP4: D5:C31.2, D5:R37.1, X1.16
IP5: D6:C31.2, D6:R37.1, X1.12
IP6: D7:C31.2, D7:R37.1, X1.8
IP7: D8:C31.2, D8:R37.1, X1.4
unnamed: C1.1, R4.1, R6.2, U1.1
unnamed: IC1.1, R2.1, R3.2
unnamed: LED1.C, R1.2
unnamed: LED2.C, R7.2
unnamed: R8.2, X3.1
unnamed: R15.1, T14.TP, U3.11
unnamed: R5.2, R6.1, U1.4
unnamed: R17.2, U3.6
unnamed: R13.1, U4.6
unnamed: C2.1, R10.1, R12.2, U2.1
unnamed: R11.2, R12.1, U2.4
unnamed: R16.1, T15.TP, U3.1
unnamed: IC2.1, R30.1, R31.2
ON0: D1:R45.2, X5.A12
ON1: D2:R45.2, X5.C12
ON2: D3:R45.2, X5.A9
ON3: D4:R45.2, X5.C9
ON4: D5:R45.2, X5.A6
ON5: D6:R45.2, X5.C6
ON6: D7:R45.2, X5.C3
ON7: D8:R45.2, X5.A3
OP0: D1:R35.2, X5.A11
OP1: D2:R35.2, X5.C11
OP2: D3:R35.2, X5.A8
OP3: D4:R35.2, X5.C8
OP4: D5:R35.2, X5.A5
OP5: D6:R35.2, X5.C5
OP6: D7:R35.2, X5.C2
OP7: D8:R35.2, X5.A2
PWRGND: R20.2, X5.A30, X5.B29, X5.B30, X5.C30
SCL: R38.1, SCL.TP, U1.2, U2.2, U4.5, U5.2, U8.2
SCLEXT: R32.1, U8.3, X4.3, X5.C29
SDA: R37.1, SDA.TP, U1.3, U2.3, U4.4, U5.1, U8.7
SDAEXT: R33.1, U8.6, X4.2, X5.A29
V5: C20.2, D1:C1.2, D1:C2.2, D1:U1.3, D2:C1.2, D2:C2.2, D2:U1.3, D3:C1.2, D3:C2.2, D3:U1.3, D4:C1.2, D4:C2.2, D4:U1.3, D5:C1.2, D5:C2.2, D5:U1.3, D6:C1.2, D6:C2.2, D6:U1.3, D7:C1.2, D7:C2.2, D7:U1.3, D8:C1.2, D8:C2.2, D8:U1.3, IC2.2, IC2.4, LED1.A, R30.2, T17.TP
V5D: C4.2, C5.1, C6.1, C7.1, C8.1, C18.1, IC1.2, IC1.4, LED2.A, R2.2, R4.2, R10.2, R13.2, R14.2, R16.2, R37.2, R38.2, T5.TP, U3.3, U4.3, U5.8, U8.8
VBIAS: D1:R36.2, D2:R36.2, D3:R36.2, D4:R36.2, D5:R36.2, D6:R36.2, D7:R36.2, D8:R36.2, R9.1, U3.8, VB.TP
VEXT: R14.1, R32.2, R33.2, X4.1, X5.A32, X5.B32, X5.C32
VEXT2: X5.A31, X5.B31, X5.C31
VIN+: C3.2, C19.2, IC1.3, IC2.3, T4.TP, X2.1
VTR1: D1:R48.1, U1.6
VTR2: D2:R48.1, U1.7
VTR3: D3:R48.1, U1.8
VTR4: D4:R48.1, U1.9
VTR5: D5:R48.1, U2.6
VTR6: D6:R48.1, U2.7
VTR7: D7:R48.1, U2.8
VTR8: D8:R48.1, U2.9

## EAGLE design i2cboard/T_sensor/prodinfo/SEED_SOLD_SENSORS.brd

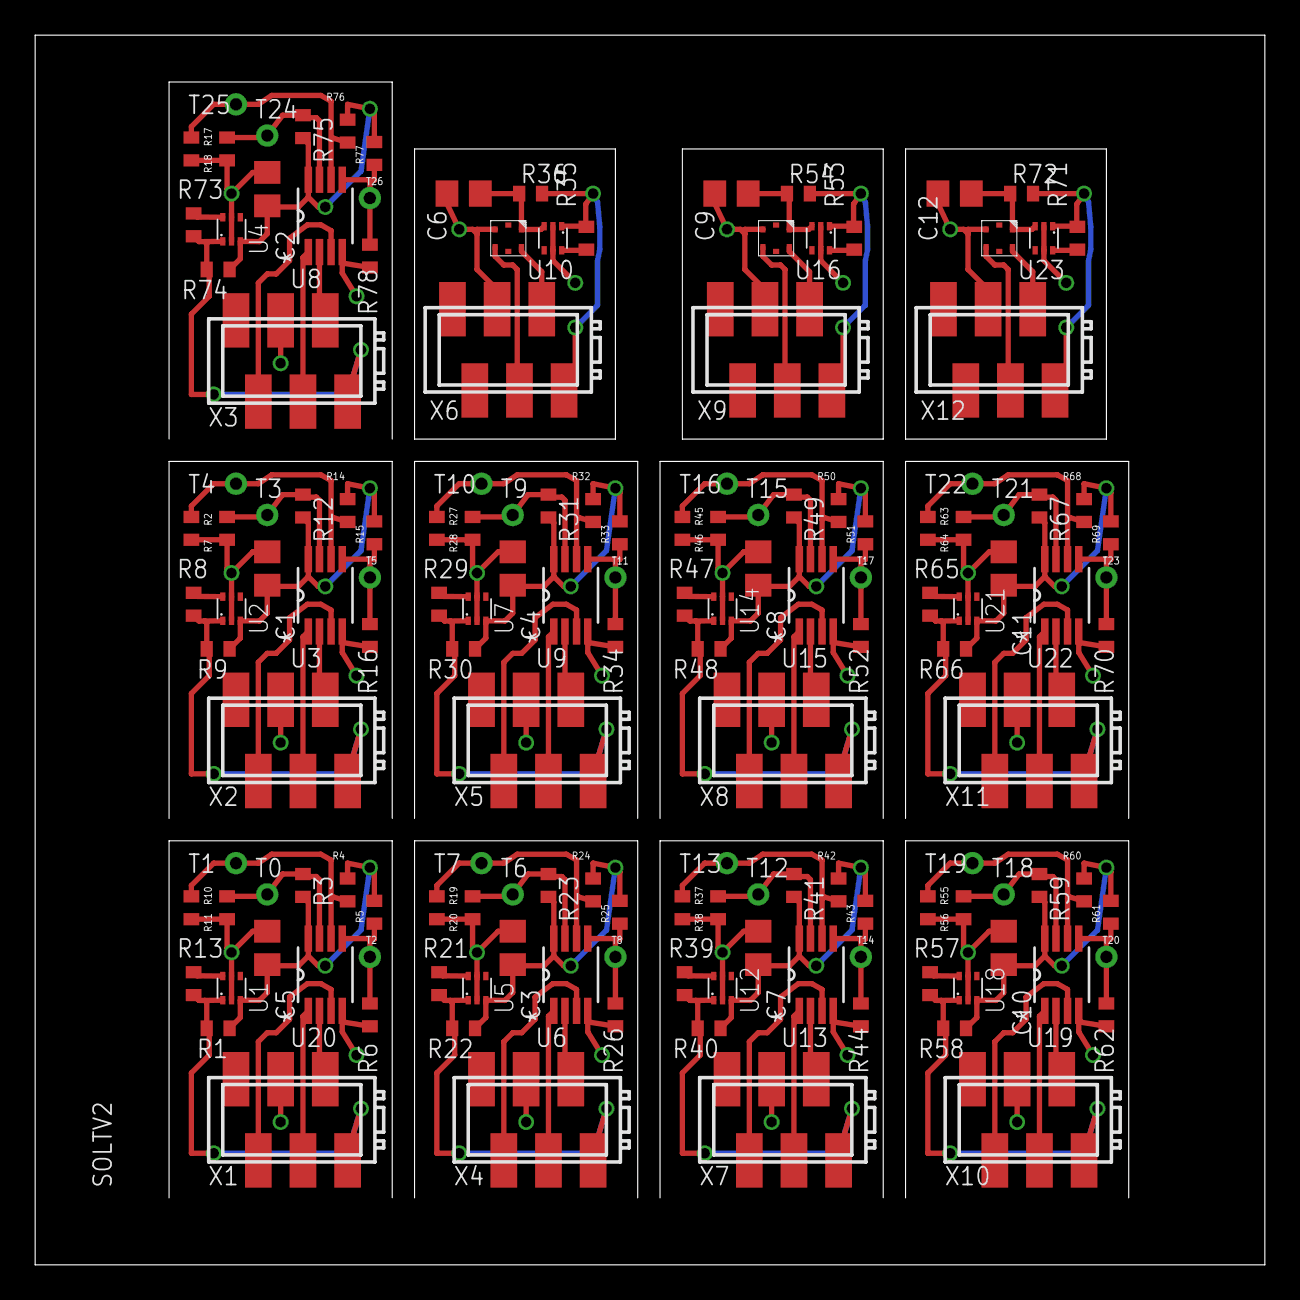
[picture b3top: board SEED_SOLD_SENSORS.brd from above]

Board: 2 copper layers, 70.0 x 70.0 mm, 153 parts (0 on the bottom side), 108 nets.

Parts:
C1, C2, C3, C4, C5, C6, C7, C8, C9, C10, C11, C12: 100n; C0805
R1, R9, R22, R30, R40, R48, R58, R66, R74: 0R; R0402
R2, R6, R7, R10, R11, R16, R17, R18, R19, R20, R26, R27, R28, R34, R37, R38, R44, R45, R46, R52, R55, R56, R62, R63, R64, R70, R78: 1K; R0402
R3, R4, R5, R8, R12, R13, R14, R15, R21, R23, R24, R25, R29, R31, R32, R33, R35, R36, R39, R41, R42, R43, R47, R49, R50, R51, R53, R54, R57, R59, R60, R61, R65, R67, R68, R69, R71, R72, R73, R75, R76, R77: 10K; R0402
T0, T1, T2, T3, T4, T5, T6, T7, T8, T9, T10, T11, T12, T13, T14, T15, T16, T17, T18, T19, T20, T21, T22, T23, T24, T25, T26: UA_TPPAD1-13; UA_P1-13
U1, U2, U4, U5, U7, U10, U12, U14, U16, U18, U21, U23: NCP170_3V3; SOT563
U3, U6, U8, U9, U13, U15, U19, U20, U22: AT30TSE752-XM8-B; SOP65P490X110-8N
U11, U17, U24: HTS221; HLGA-6
X1, X2, X3, X4, X5, X6, X7, X8, X9, X10, X11, X12: MICROMATCH-6SMD; MICROMATCH_SMD-6

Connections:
GND: C5.1, R6.1, R10.1, R11.1, U1.2, U1.5, U20.4, X1.4
GND1: C1.1, R2.1, R7.1, R16.1, U2.2, U2.5, U3.4, X2.4
GND2: C2.1, R17.1, R18.1, R78.1, U4.2, U4.5, U8.4, X3.4
GND3: C3.1, R19.1, R20.1, R26.1, U5.2, U5.5, U6.4, X4.4
GND4: C4.1, R27.1, R28.1, R34.1, U7.2, U7.5, U9.4, X5.4
GND5: C6.1, U10.2, U10.5, U11.5, X6.4
GND6: C7.1, R37.1, R38.1, R44.1, U12.2, U12.5, U13.4, X7.4
GND7: C8.1, R45.1, R46.1, R52.1, U14.2, U14.5, U15.4, X8.4
GND8: C9.1, U16.2, U16.5, U17.5, X9.4
GND9: C10.1, R55.1, R56.1, R62.1, U18.2, U18.5, U19.4, X10.4
GND10: C11.1, R63.1, R64.1, R70.1, U21.2, U21.5, U22.4, X11.4
GND11: C12.1, U23.2, U23.5, U24.5, X12.4
unnamed: R5.1, R6.2, T2.TP, U20.5
unnamed: R4.1, R11.2, T1.TP, U20.6
unnamed: R3.1, R10.2, T0.TP, U20.7
unnamed: R8.1, U2.6
unnamed: R15.1, R16.2, T5.TP, U3.5
unnamed: R7.2, R14.1, T4.TP, U3.6
unnamed: R13.1, U1.6
unnamed: R2.2, R12.1, T3.TP, U3.7
unnamed: R73.1, U4.6
unnamed: R21.1, U5.6
unnamed: R25.1, R26.2, T8.TP, U6.5
unnamed: R20.2, R24.1, T7.TP, U6.6
unnamed: R19.2, R23.1, T6.TP, U6.7
unnamed: R29.1, U7.6
unnamed: R33.1, R34.2, T11.TP, U9.5
unnamed: R28.2, R32.1, T10.TP, U9.6
unnamed: R27.2, R31.1, T9.TP, U9.7
unnamed: R35.1, U10.6
unnamed: R39.1, U12.6
unnamed: R43.1, R44.2, T14.TP, U13.5
unnamed: R38.2, R42.1, T13.TP, U13.6
unnamed: R37.2, R41.1, T12.TP, U13.7
unnamed: R47.1, U14.6
unnamed: R51.1, R52.2, T17.TP, U15.5
unnamed: R46.2, R50.1, T16.TP, U15.6
unnamed: R45.2, R49.1, T15.TP, U15.7
unnamed: R53.1, U16.6
unnamed: R57.1, U18.6
unnamed: R61.1, R62.2, T20.TP, U19.5
unnamed: R56.2, R60.1, T19.TP, U19.6
unnamed: R55.2, R59.1, T18.TP, U19.7
unnamed: R65.1, U21.6
unnamed: R69.1, R70.2, T23.TP, U22.5
unnamed: R64.2, R68.1, T22.TP, U22.6
unnamed: R63.2, R67.1, T21.TP, U22.7
unnamed: R71.1, U23.6
unnamed: R77.1, R78.2, T26.TP, U8.5
unnamed: R18.2, R76.1, T25.TP, U8.6
unnamed: R17.2, R75.1, T24.TP, U8.7
SCL_L: U20.2, X1.2
SCL_L1: U3.2, X2.2
SCL_L2: U8.2, X3.2
SCL_L3: U6.2, X4.2
SCL_L4: U9.2, X5.2
SCL_L5: U11.2, X6.2
SCL_L6: U13.2, X7.2
SCL_L7: U15.2, X8.2
SCL_L8: U17.2, X9.2
SCL_L9: U19.2, X10.2
SCL_L10: U22.2, X11.2
SCL_L11: U24.2, X12.2
SDA_L: U20.1, X1.3
SDA_L1: U3.1, X2.3
SDA_L2: U8.1, X3.3
SDA_L3: U6.1, X4.3
SDA_L4: U9.1, X5.3
SDA_L5: U11.4, X6.3
SDA_L6: U13.1, X7.3
SDA_L7: U15.1, X8.3
SDA_L8: U17.4, X9.3
SDA_L9: U19.1, X10.3
SDA_L10: U22.1, X11.3
SDA_L11: U24.4, X12.3
TALERT: U20.3, X1.5
TALERT1: U3.3, X2.5
TALERT2: U8.3, X3.5
TALERT3: U6.3, X4.5
TALERT4: U9.3, X5.5
TALERT6: U13.3, X7.5
TALERT7: U15.3, X8.5
TALERT9: U19.3, X10.5
TALERT10: U22.3, X11.5
V3_3L: C5.2, R1.1, R3.2, R4.2, R5.2, U1.3, U20.8
V3_3L1: C1.2, R9.1, R12.2, R14.2, R15.2, U2.3, U3.8
V3_3L2: C2.2, R74.1, R75.2, R76.2, R77.2, U4.3, U8.8
V3_3L3: C3.2, R22.1, R23.2, R24.2, R25.2, U5.3, U6.8
V3_3L4: C4.2, R30.1, R31.2, R32.2, R33.2, U7.3, U9.8
V3_3L5: C6.2, R36.1, U10.3, U11.1
V3_3L6: C7.2, R40.1, R41.2, R42.2, R43.2, U12.3, U13.8
V3_3L7: C8.2, R48.1, R49.2, R50.2, R51.2, U14.3, U15.8
V3_3L8: C9.2, R54.1, U16.3, U17.1
V3_3L9: C10.2, R58.1, R59.2, R60.2, R61.2, U18.3, U19.8
V3_3L10: C11.2, R66.1, R67.2, R68.2, R69.2, U21.3, U22.8
V3_3L11: C12.2, R72.1, U23.3, U24.1
V5F: R1.2, R13.2, U1.1, X1.1
V5F1: R8.2, R9.2, U2.1, X2.1
V5F2: R73.2, R74.2, U4.1, X3.1
V5F3: R21.2, R22.2, U5.1, X4.1
V5F4: R29.2, R30.2, U7.1, X5.1
V5F5: R35.2, R36.2, U10.1, X6.1
V5F6: R39.2, R40.2, U12.1, X7.1
V5F7: R47.2, R48.2, U14.1, X8.1
V5F8: R53.2, R54.2, U16.1, X9.1
V5F9: R57.2, R58.2, U18.1, X10.1
V5F10: R65.2, R66.2, U21.1, X11.1
V5F11: R71.2, R72.2, U23.1, X12.1

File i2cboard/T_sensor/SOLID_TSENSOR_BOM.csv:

SOLID Temperature  sensor;;V 2.0;;;;;;;;;;
Resistors 1%  in not indicated otherwise;;;;;;;;;;;;
Capicitors  10V  / 20 %  if not indicated otherwise;;;;;;;;;;;;
value NC means do not place;;;;;;;;;;;;
Qty;Value;Device;Package;Parts;Description;MPN;OC_FARNELL;OC_NEWARK;PACKAGE;PARTNO;SUPPLIER;TP_SIGNAL_NAME
1;0R;R-EU_R0402;R0402;R1;RESISTOR, European symbol;;;;;;;
1;100n;C-EUC0805;C0805;C5;CAPACITOR, European symbol;;;;;*;;
4;10K;R-EU_R0402;R0402;R3, R4, R5, R13;RESISTOR, European symbol;;;;;;;
3;1K;R-EU_R0402;R0402;R6, R10, R11;RESISTOR, European symbol;;;;;;;
1;AT30TSE752-XM8-B;AT30TSE752-XM8-B;SOP65P490X110-8N;U20;SENSOR, TEMP, 9-12BIT, 2KB EEPROM, MSOP-8;AT30TSE752-XM8-B;2115206;Unknown;MSOP-8;;ATMEL;
1;MICROMATCH-6SMD;MICROMATCH-6SMD;MICROMATCH_SMD-6;X1;MicroMaTch 6  7-215464-6 / 0-215464-6;7-188275-6;1056234;;;;;
1;NC;NCP170;SOT563;U1;;NCP170AXV330T2G;2507604;;;;ON;
2;NC;UA_TPPAD1-13;UA_P1-13;T0, T1;Test pad;;;;;*;;

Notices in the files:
i2cboard/T_sensor/prodinfo/SEED_SOLD_SENSORS.brd:
(C) 2016  nov
(C) 2016 Universiteit Antwerpen
parts and their libraries:
SparkFun-Passives: Licensing: Creative Commons ShareAlike 4.0 International - https://creativecommons.org/licenses/by-sa/4.0
